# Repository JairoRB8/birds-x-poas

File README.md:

# Poás Team BIRDS-X Competition PCB Source Files

PCB source files for Poás team submission for the BIRDS-X APRS Payload Competition.
The PCB was developed using the latest (as of December 2023) version of Eagle in Fusion 360. The PCBs were manufactured and assembled at JLCPCB. Components not in stock at JLCPC were assembled manually.

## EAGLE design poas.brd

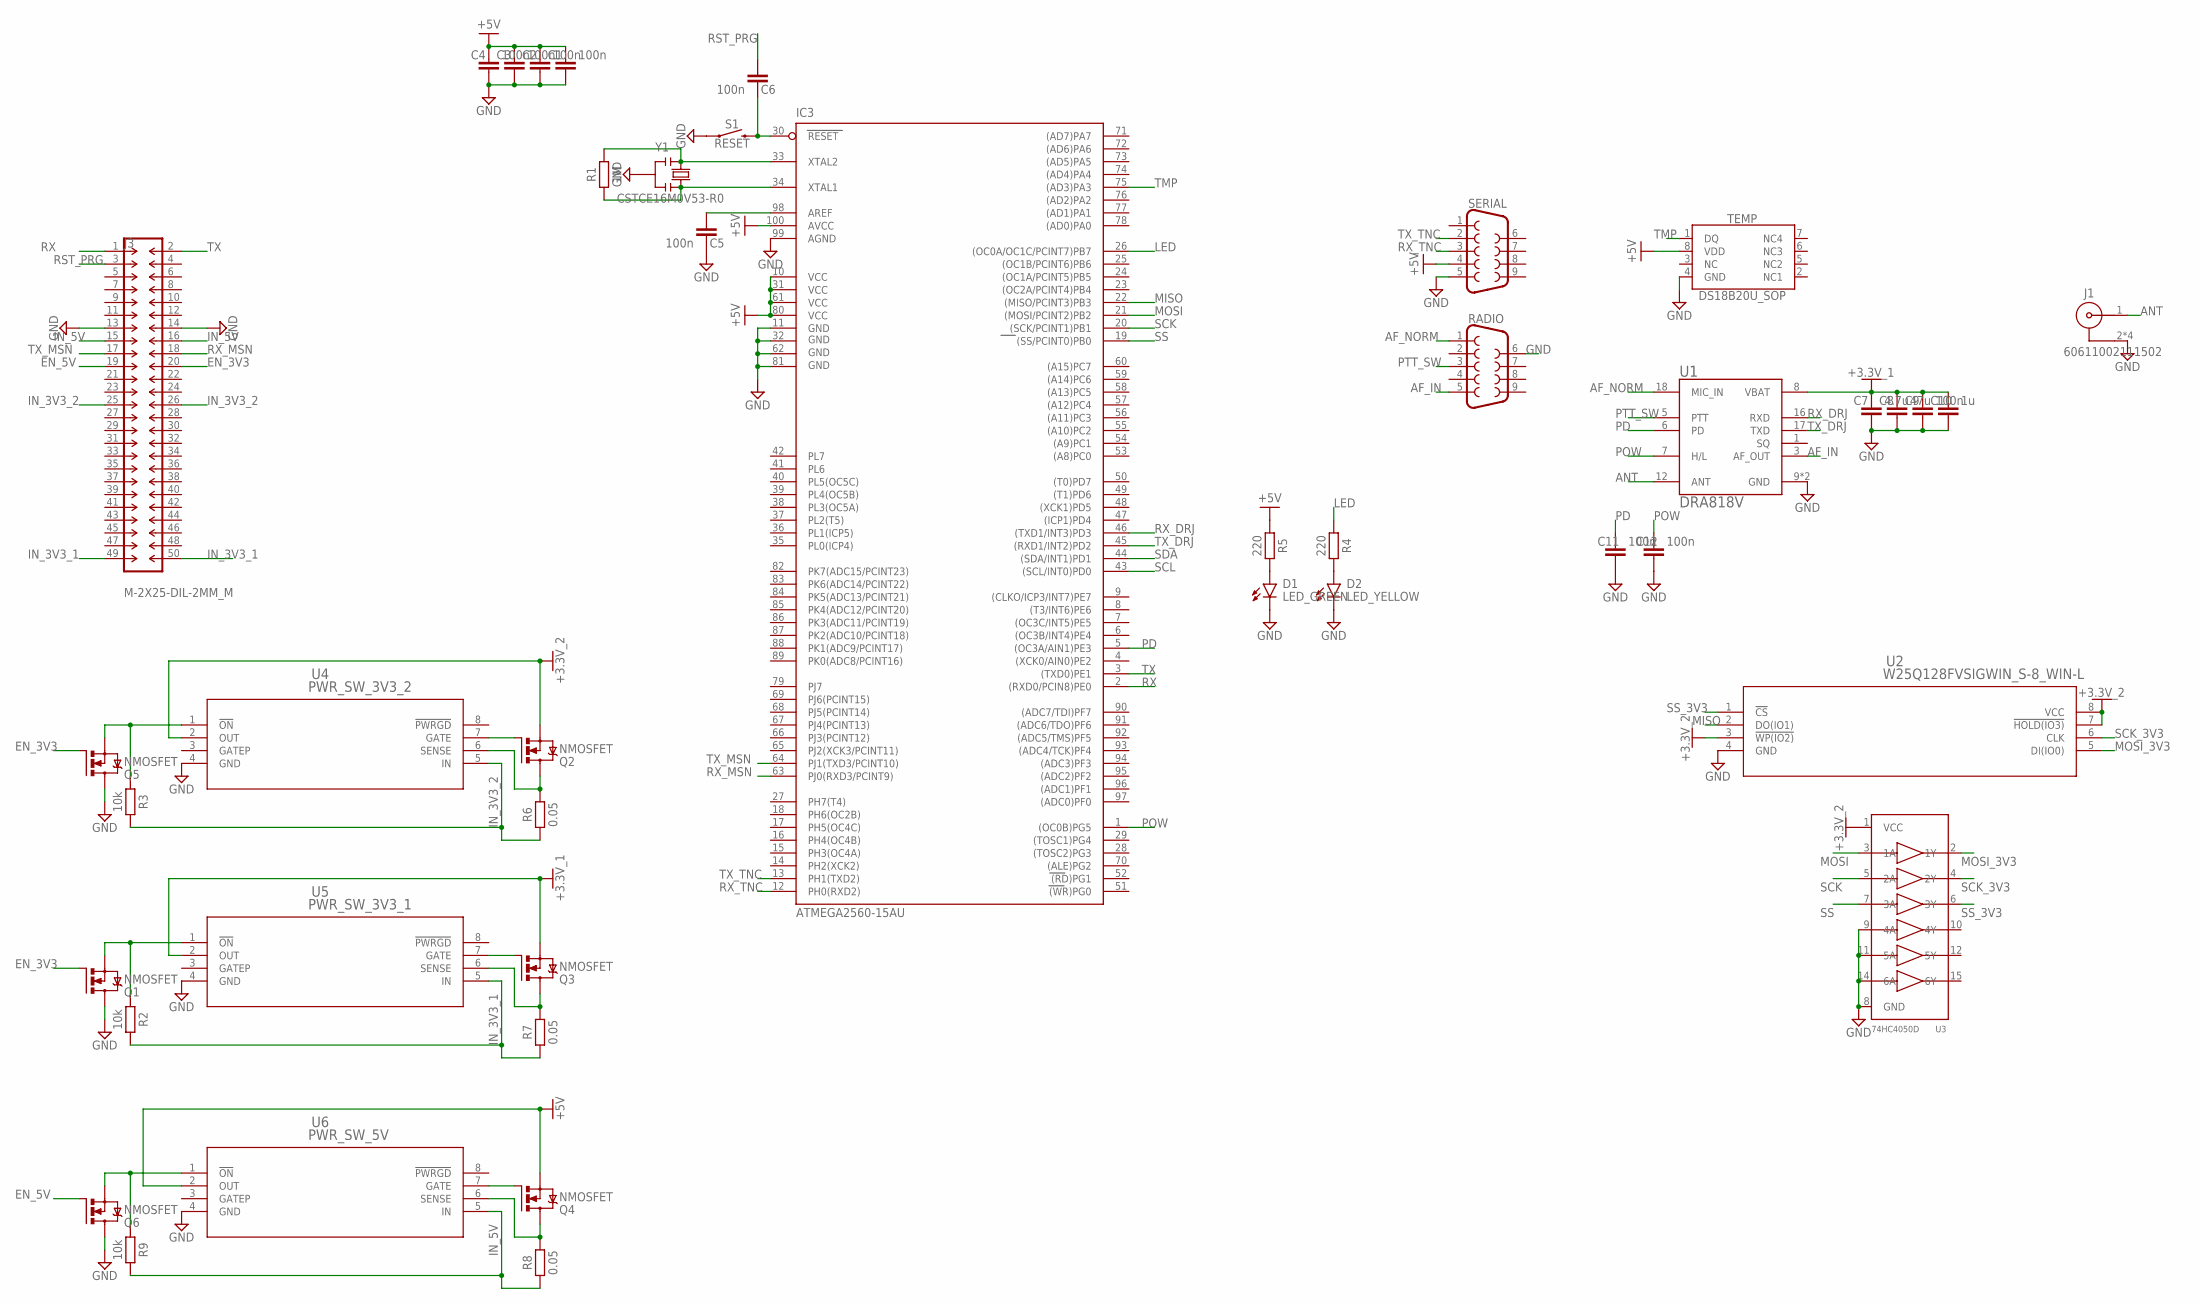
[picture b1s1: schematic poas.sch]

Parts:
C1, C2, C3, C4, C5, C6, C9, C11, C12: 100n; CAPC1608X85
C7: 4.7u; CAPC1608X85
C8: 47u; CAPC1608X85
C10: 1u; CAPC1608X85
D1: LED_GREEN; LEDC1608X55N_FLAT-G
D2: LED_YELLOW; LEDC1608X55N_FLAT-Y
IC3: ATMEGA2560-15AU; TQFP100
J1: 60611002111502
J3: M-2X25-DIL-2MM_M; DIL-2MM-2X25_M
Q1, Q2, Q3, Q4, Q5, Q6: NMOSFET; SOT23
R1: 1M; RESC1608X60
R2, R3, R9: 10k; RESC1608X60
R4, R5: 220; RESC1608X60
R6, R7, R8: 0.05; RESC1608X60
RADIO: DB9MALE; DB9_MALE
S1: RESET; TACTILE_SWITCH_SMD_6.2MM_TALL
SERIAL: DB9MALE; DB9_MALE
TEMP: DS18B20U_SOP; SOP65P491X110-8N
U1: DRA818V; DORJI_DRA818V
U2: W25Q128FVSIGWIN_S-8_WIN-L; WIN_S-8_WIN-L
U3: 74HC4050D; TSSOP16
U4: PWR_SW_3V3_2; TSOT-23_TS8_LIT-L
U5: PWR_SW_3V3_1; TSOT-23_TS8_LIT-L
U6: PWR_SW_5V; TSOT-23_TS8_LIT-L
Y1: CSTCE16M0V53-R0; RESONATOR

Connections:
+3.3V_1: C7.1, C8.1, C9.1, C10.1, Q3.2 (S), U1.8 (VBAT), U5.2 (OUT)
+3.3V_2: Q2.2 (S), U2.3 (!WP(IO2)), U2.7 (!HOLD(IO3)), U2.8 (VCC), U3.1 (VCC), U4.2 (OUT)
+5V: C1.1, C2.1, C3.1, C4.1, IC3.10 (VCC), IC3.31 (VCC1), IC3.61 (VCC2), IC3.80 (VCC3), IC3.100 (AVCC), Q4.2 (S), R5.1, SERIAL.4, TEMP.8 (VDD), U6.2 (OUT)
AF_IN: RADIO.5, U1.3 (AF_OUT)
AF_NORM: RADIO.1, U1.18 (MIC_IN)
ANT: J1.1, U1.12 (ANT)
EN_3V3: J3.20, Q1.1 (G), Q5.1 (G)
EN_5V: J3.19, Q6.1 (G)
GND: C1.2, C2.2, C3.2, C4.2, C5.1, C7.2, C8.2, C9.2, C10.2, C11.2, C12.2, D1.C, D2.C, IC3.11 (GND), IC3.32 (GND1), IC3.62 (GND2), IC3.81 (GND3), IC3.99 (AGND), J1.2, J1.3 (2), J1.4 (2), J1.5 (2), J3.13, J3.14, Q1.3 (D), Q5.3 (D), Q6.3 (D), RADIO.6, S1.A2 (1), SERIAL.5, TEMP.4 (GND), U1.9 (GND), U1.10 (GND), U2.4 (GND), U3.8 (GND), U3.9 (4A), U3.11 (5A), U3.14 (6A), U4.4 (GND), U5.4 (GND), U6.4 (GND), Y1.2
IN_3V3_1: J3.49, J3.50, R2.2, R7.1, U5.5 (IN)
IN_3V3_2: J3.25, J3.26, R3.2, R6.1, U4.5 (IN)
IN_5V: J3.15, J3.16, R8.1, R9.2, U6.5 (IN)
LED: IC3.26 ((OC0A/OC1C/PCINT7)PB7), R4.1
MISO: IC3.22 ((MISO/PCINT3)PB3), U2.2 (DO(IO1))
MOSI: IC3.21 ((MOSI/PCINT2)PB2), U3.3 (1A)
MOSI_3V3: U2.5 (DI(IO0)), U3.2 (1Y)
unnamed: C5.2, IC3.98 (AREF)
unnamed: Q5.2 (S), R3.1, U4.1 (!ON)
unnamed: Q1.2 (S), R2.1, U5.1 (!ON)
unnamed: D1.A, R5.2
unnamed: D2.A, R4.2
unnamed: Q2.1 (G), U4.7 (GATE)
unnamed: Q2.3 (D), R6.2, U4.6 (SENSE)
unnamed: Q3.1 (G), U5.7 (GATE)
unnamed: Q3.3 (D), R7.2, U5.6 (SENSE)
unnamed: Q4.1 (G), U6.7 (GATE)
unnamed: Q4.3 (D), R8.2, U6.6 (SENSE)
unnamed: Q6.2 (S), R9.1, U6.1 (!ON)
PD: C11.1, IC3.5 ((OC3A/AIN1)PE3), U1.6 (PD)
POW: C12.1, IC3.1 ((OC0B)PG5), U1.7 (H/L)
PTT_SW: RADIO.3, U1.5 (PTT)
RESET: C6.1, IC3.30 (RESET), S1.B2 (2)
RST_PRG: C6.2, J3.3
RX: IC3.2 ((RXD0/PCIN8)PE0), J3.1
RX_DRJ: IC3.46 ((TXD1/INT3)PD3), U1.16 (RXD)
RX_MSN: IC3.63 (PJ0(RXD3/PCINT9)), J3.18
RX_TNC: IC3.12 (PH0(RXD2)), SERIAL.3
SCK: IC3.20 ((SCK/PCINT1)PB1), U3.5 (2A)
SCK_3V3: U2.6 (CLK), U3.4 (2Y)
SCL: IC3.43 ((SCL/INT0)PD0)
SDA: IC3.44 ((SDA/INT1)PD1)
SS: IC3.19 ((SS/PCINT0)PB0), U3.7 (3A)
SS_3V3: U2.1 (!CS), U3.6 (3Y)
TMP: IC3.75 ((AD3)PA3), TEMP.1 (DQ)
TX: IC3.3 ((TXD0)PE1), J3.2
TX_DRJ: IC3.45 ((RXD1/INT2)PD2), U1.17 (TXD)
TX_MSN: IC3.64 (PJ1(TXD3/PCINT10)), J3.17
TX_TNC: IC3.13 (PH1(TXD2)), SERIAL.2
XTAL1: IC3.33 (XTAL2), R1.2, Y1.1
XTAL2: IC3.34 (XTAL1), R1.1, Y1.3

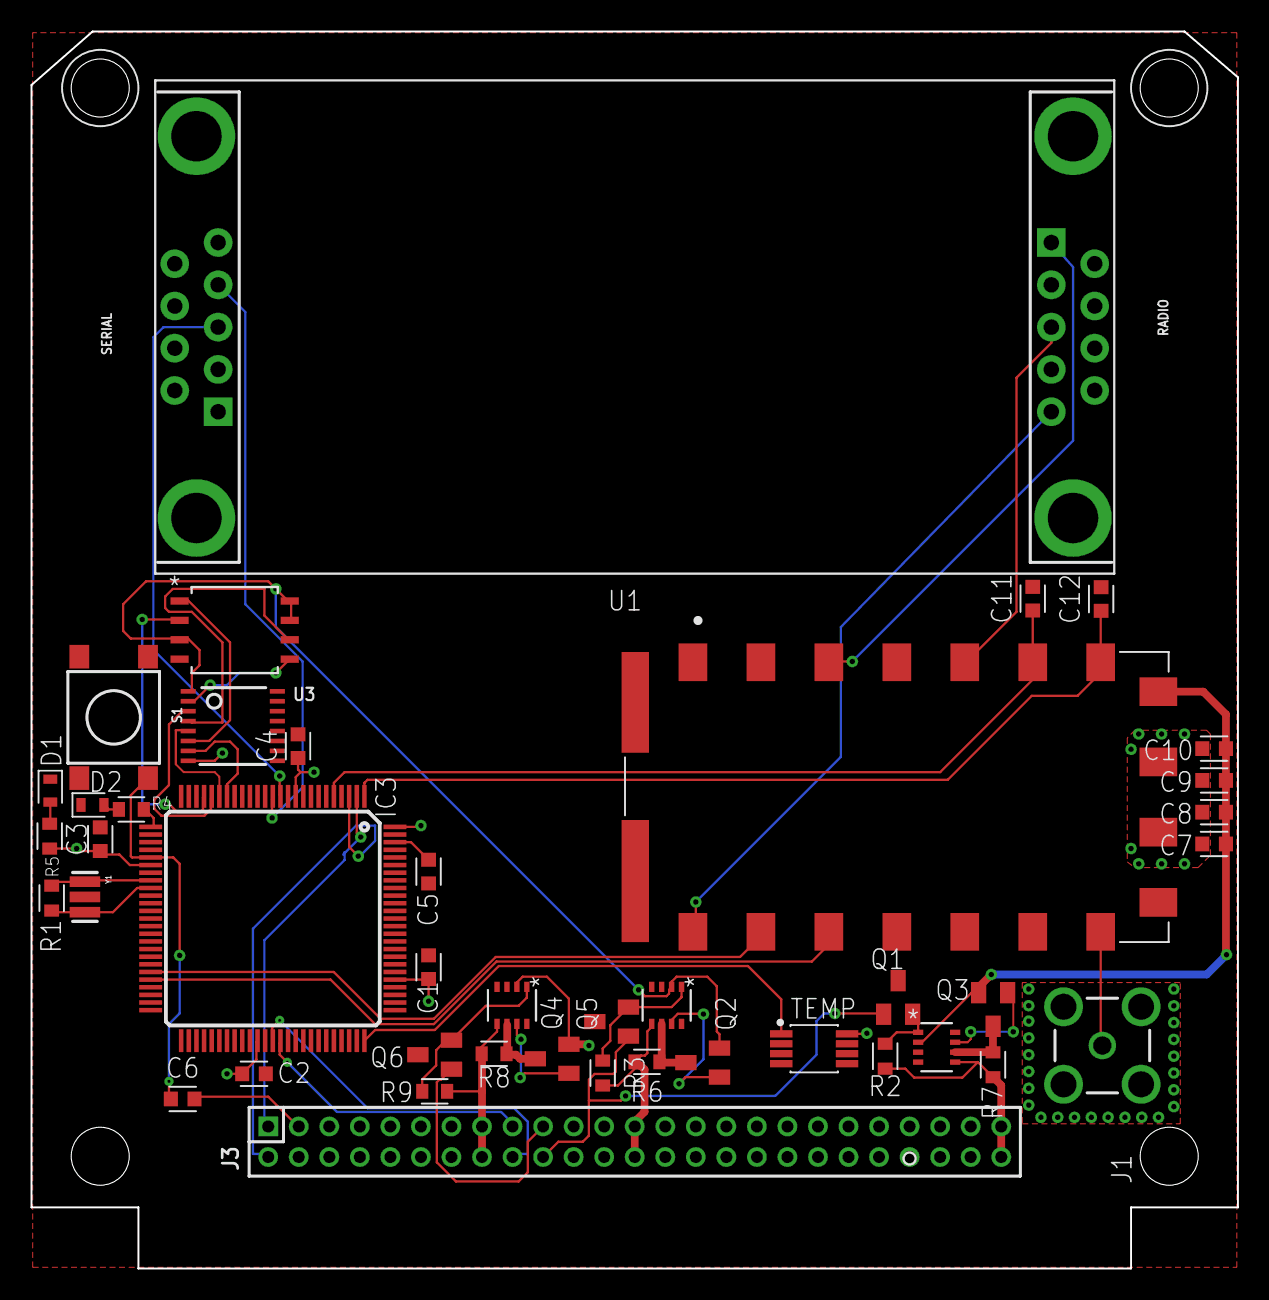
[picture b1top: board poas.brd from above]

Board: 4 copper layers, 79.0 x 81.0 mm, 43 parts (0 on the bottom side), 48 nets.

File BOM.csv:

Comment,Device,Footprint,Designator
,DB9MALE,DB9_MALE,"RADIO, SERIAL"
0.05,R_CHIP-0603(1608-METRIC),R0603,"R6, R7, R8"
100n,C_CHIP-0603(1608-METRIC),C0603,"C1, C2, C3, C4, C5, C6, C9, C11, C12"
10k,R_CHIP-0603(1608-METRIC),R0603,"R2, R3, R9"
1M,R_CHIP-0603(1608-METRIC),R0603,R1
1u,C_CHIP-0603(1608-METRIC),C0603,C10
220,R_CHIP-0603(1608-METRIC),R0603,"R4, R5"
4.7u,C_CHIP-0603(1608-METRIC),C0603,C7
47u,C_CHIP-0603(1608-METRIC),C0603,C8
Antenna,6.0611E+13,6.0611E+13,J1
74HC4050D,74HC4050DTSSOP,TSSOP16,U3
ATMEGA2560-15AU,0023_ATMEGA2560-16AU,TQFP100,IC3
CSTCE16M0V53-R0,0011_CSTCE16M0V53-R0,RESONATOR,Y1
DRA818V,DRA818V,DORJI_DRA818V,U1
DS18B20U_SOP,DS18B20U_SOP,SOP65P491X110-8N,TEMP
LED_GREEN,CHIP-FLAT-G_0603-0.55MM,LEDC1608X55N_FLAT-G,D1
LED_YELLOW,CHIP-FLAT-Y_0603-0.55MM,LEDC1608X55N_FLAT-Y,D2
M-2X25-DIL-2MM_M,M-2X25-DIL-2MM_M,DIL-2MM-2X25_M,J3
NMOSFET,NMOSFETSOT23-GSD,SOT23,"Q1, Q2, Q3, Q4, Q5, Q6"
PWR_SW_3V3_1,LTC4361CTS8-2TRMPBFTSOT-23_TS8_LIT-L,TSOT-23_TS8_LIT-L,U5
PWR_SW_3V3_2,LTC4361CTS8-2TRMPBFTSOT-23_TS8_LIT-L,TSOT-23_TS8_LIT-L,U4
PWR_SW_5V,LTC4361CTS8-2TRMPBFTSOT-23_TS8_LIT-L,TSOT-23_TS8_LIT-L,U6
RESET,MOMENTARY-SWITCH-SPST-SMD-6.2MM-TALL,TACTILE_SWITCH_SMD_6.2MM_TALL,S1
W25Q128FVSIGWIN_S-8_WIN-L,W25Q128FVSIGWIN_S-8_WIN-L,WIN_S-8_WIN-L,U2

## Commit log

2024-03-06 Initial commit
    Find the Fusion 360 project and individual schematic and board files in the repository. Furthermore, the PnP and BOM files used for assembly at JLCPCB have been added as well.

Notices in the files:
parts and their libraries:
SparkFun-Switches: Licensing: Creative Commons ShareAlike 4.0 International - https://creativecommons.org/licenses/by-sa/4.0
microbuilder: This work is placed in the public domain, and may be freely used for commercial and non-commercial work with the following conditions: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
